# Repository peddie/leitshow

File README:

0) Purpose

This project is a music-synced lightshow.  It attempts to map an audio
stream onto a series of intensity commands for channels, presumably
then connected to lights, in a way that makes the light/music
combination entertaining.

1) Build process

Type `make'.  

You will need FFTW3 and PulseAudio development files installed; on
civilized systems these are available as `libfftw3-dev' and
`libpulse-dev'.  The makefile wants gcc-4.5; if you don't have it, you
can change that to just `gcc' and remove `-flto' from the definition
of `OPTFLAGS'.  

1.1) Portability

Nope.  

2) Usage

Type `./leitshow'.  

You will most likely want the PulseAudio utility called `pavucontrol',
which lets you choose what audio stream to send to the lightshow
program.  When I don't explicitly assign a channel with pavucontrol,
pulseaudio seems to give the lightshow the microphone audio stream by
default.

3) Customization

The lightshow will attempt to send commands via /dev/ttyUSB0.  You can
change this, along with the number of channels and a few other things,
in the #defines section at the beginning of `test.c'.

4) Hardware

The hardware matters little, as long as you have a device that can
listen for the code word and then read channel intensities and turn
them into fet duty cycles.

4.1) Example setup (at the Oasis):

Henry set up a bunch of cheap LED rolls from china to be driven by a
dsPIC motor controller board.  We elected to use 3 channels (R, G, B),
so the PIC simply receives the code word followed by 3 8-bit values
that indicate the desired intensity for each channel.  The motor
controller board already has 3 channels for driving brushless motors,
so we just directly translate the intensity commands to duty cycles.
We connect the LED rolls to a 12V power supply through the motor
control phases, and we're done.  

5) Bugs

PulseAudio seems to like to send the program the microphone stream
rather than the music stream.  Not sure if this can be worked around
or if I need to switch to using JACK.  

The lightshow doesn't work that well as a music-synced lightshow; it's
not that enjoyable to watch.  More algorithm development is needed.

6) Thanks

This lightshow is a crappy approximation of the one at tEp at MIT.
Almost every aspect of it was inspired by the tEp one, and if I hadn't
worked on a few of the incarnations of the tEp lightshow, this would
have taken a lot longer.  That lightshow was written, at various
times, by Frostbyte, Penguin, sMark, Elmo and Knosepiq.

Henry Hallam, as is his custom, got all the hardware working in a
remarkably short period of time.

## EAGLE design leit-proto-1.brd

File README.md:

leitshow
========

Light show PCBs (and code?)

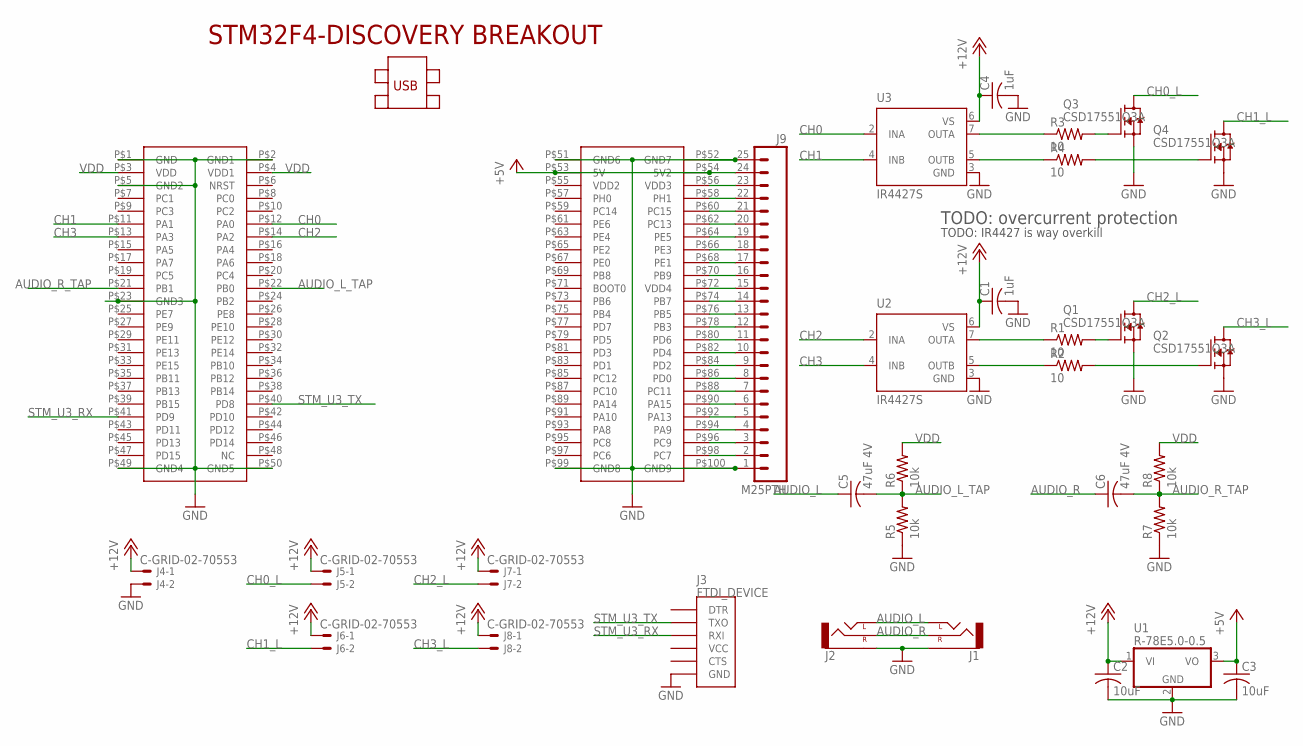
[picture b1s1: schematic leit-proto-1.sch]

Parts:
C1, C4: 1uF; C0603
C2, C3: 10uF; C0805
C5, C6: 47uF 4V; C0805
J1, J2: AUDIO-JACKPTH; AUDIO-JACK
J3: FTDI_DEVICE; FTDI_DEVICE_SIDE
J4, J5, J6, J7, J8: C-GRID-02-70553; 70553-02
J9: M25PTH; 1X25
MOD1: STM32F4-DISCOVERY
Q1, Q2, Q3, Q4: CSD17551Q3A; SON3.3
R1, R2, R3, R4: 10; R0603
R5, R6, R7, R8: 10k; R0603
U1: R-78E5.0-0.5; TO220V
U2, U3: IR4427S; SO08

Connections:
+5V: C3.1, J9.24, MOD1.P$53 (5V), MOD1.P$54 (5V2), U1.3 (VO)
+12V: C1.1, C2.1, C4.1, J4.1, J5.1, J6.1, J7.1, J8.1, U1.1 (VI), U2.6 (VS), U3.6 (VS)
AUDIO_L: C5.1, J1.TIP (LEFT), J2.TIP (LEFT)
AUDIO_L_TAP: C5.2, MOD1.P$22 (PB0), R5.2, R6.1
AUDIO_R: C6.1, J1.RING (RIGHT), J2.RING (RIGHT)
AUDIO_R_TAP: C6.2, MOD1.P$21 (PB1), R7.2, R8.1
CH0: MOD1.P$12 (PA0), U3.2 (INA)
CH0_L: J5.2, Q3.5 (D), Q3.6 (D), Q3.7 (D), Q3.8 (D)
CH1: MOD1.P$11 (PA1), U3.4 (INB)
CH1_L: J6.2, Q4.5 (D), Q4.6 (D), Q4.7 (D), Q4.8 (D)
CH2: MOD1.P$14 (PA2), U2.2 (INA)
CH2_L: J7.2, Q1.5 (D), Q1.6 (D), Q1.7 (D), Q1.8 (D)
CH3: MOD1.P$13 (PA3), U2.4 (INB)
CH3_L: J8.2, Q2.5 (D), Q2.6 (D), Q2.7 (D), Q2.8 (D)
GND: C1.2, C2.2, C3.2, C4.2, J1.SLEEVE, J2.SLEEVE, J3.P$6 (GND), J4.2, J9.1, J9.25, MOD1.P$1 (GND), MOD1.P$2 (GND1), MOD1.P$5 (GND2), MOD1.P$23 (GND3), MOD1.P$49 (GND4), MOD1.P$50 (GND5), MOD1.P$51 (GND6), MOD1.P$52 (GND7), MOD1.P$99 (GND8), MOD1.P$100 (GND9), Q1.1 (S), Q1.2 (S), Q1.3 (S), Q2.1 (S), Q2.2 (S), Q2.3 (S), Q3.1 (S), Q3.2 (S), Q3.3 (S), Q4.1 (S), Q4.2 (S), Q4.3 (S), R5.1, R7.1, U1.2 (GND), U2.3 (GND), U3.3 (GND)
unnamed: R1.1, U2.7 (OUTA)
unnamed: Q1.4 (G), R1.2
unnamed: Q2.4 (G), R2.2
unnamed: R2.1, U2.5 (OUTB)
unnamed: R3.1, U3.7 (OUTA)
unnamed: Q3.4 (G), R3.2
unnamed: Q4.4 (G), R4.2
unnamed: R4.1, U3.5 (OUTB)
unnamed: J9.2, MOD1.P$98 (PC7)
unnamed: J9.3, MOD1.P$96 (PC9)
unnamed: J9.4, MOD1.P$94 (PA9)
unnamed: J9.5, MOD1.P$92 (PA13)
unnamed: J9.6, MOD1.P$90 (PA15)
unnamed: J9.7, MOD1.P$88 (PC11)
unnamed: J9.8, MOD1.P$86 (PD0)
unnamed: J9.9, MOD1.P$84 (PD2)
unnamed: J9.10, MOD1.P$82 (PD4)
unnamed: J9.11, MOD1.P$80 (PD6)
unnamed: J9.12, MOD1.P$78 (PB3)
unnamed: J9.13, MOD1.P$76 (PB5)
unnamed: J9.14, MOD1.P$74 (PB7)
unnamed: J9.15, MOD1.P$72 (VDD4)
unnamed: J9.16, MOD1.P$70 (PB9)
unnamed: J9.17, MOD1.P$68 (PE1)
unnamed: J9.18, MOD1.P$66 (PE3)
unnamed: J9.19, MOD1.P$64 (PE5)
unnamed: J9.20, MOD1.P$62 (PC13)
unnamed: J9.21, MOD1.P$60 (PC15)
unnamed: J9.22, MOD1.P$58 (PH1)
unnamed: J9.23, MOD1.P$56 (VDD3)
STM_U3_RX: J3.P$3 (RXI), MOD1.P$41 (PD9)
STM_U3_TX: J3.P$2 (TXO), MOD1.P$40 (PD8)
VDD: MOD1.P$3 (VDD), MOD1.P$4 (VDD1), R6.2, R8.2

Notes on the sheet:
TODO: overcurrent protection
TODO: IR4427 is way overkill

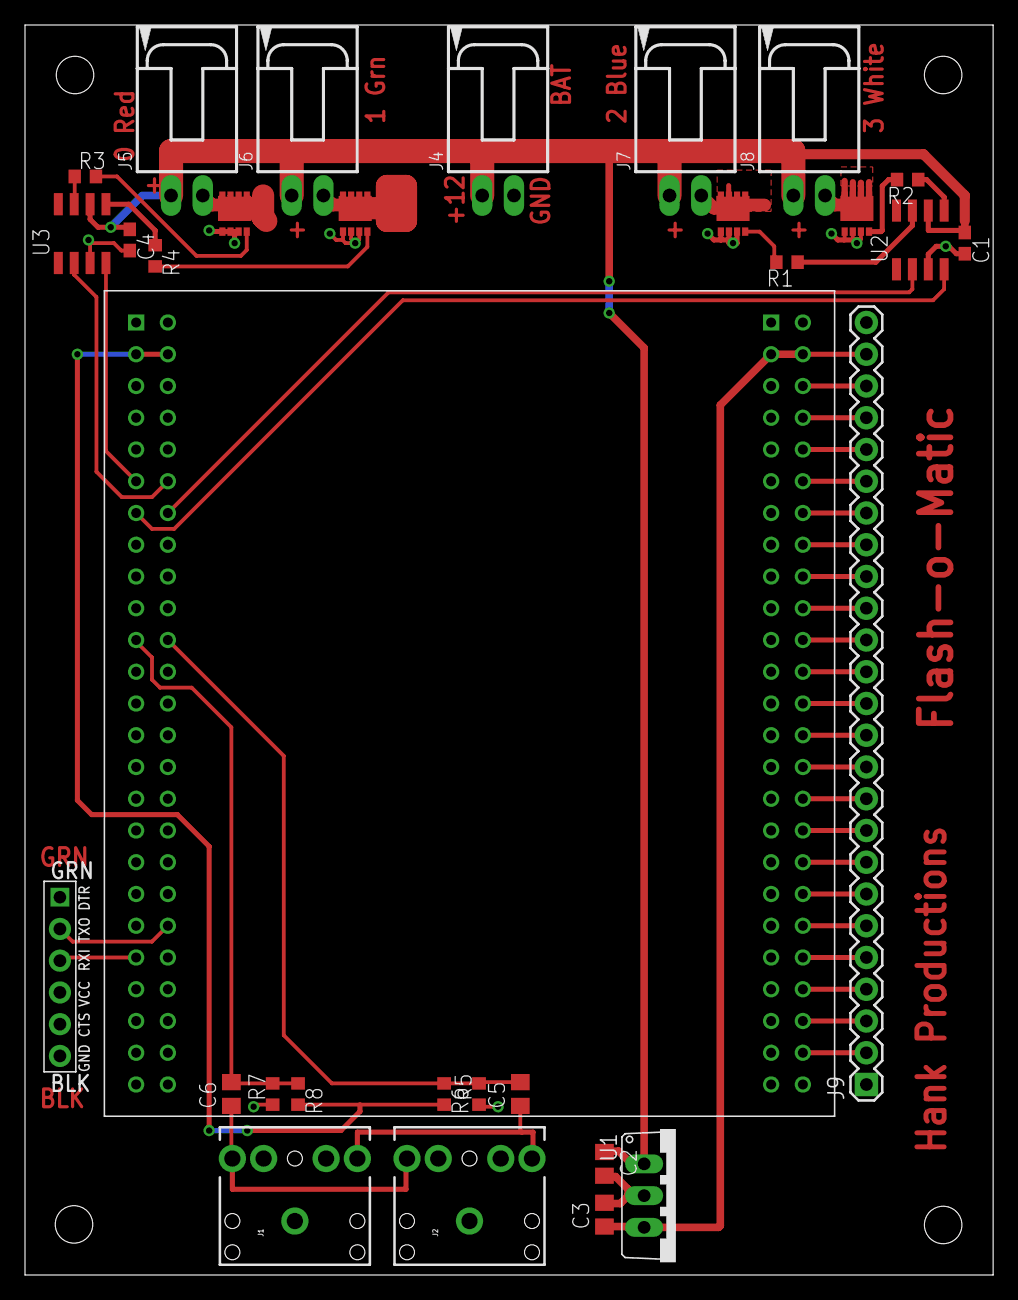
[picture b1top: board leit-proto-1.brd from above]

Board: 2 copper layers, 77.5 x 100.0 mm, 31 parts (0 on the bottom side), 48 nets.

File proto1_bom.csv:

Part,Value,Device,Package,Description,DK order code,DK qty,DK ref
C1,1uF,C-USC0603,C0603,"CAPACITOR, American symbol",311-1372-1-ND,10,Leitshow C1 C4
C2,10uF,C-USC0805,C0805,"CAPACITOR, American symbol",1276-2893-1-ND,10,Leitshow C2 C3
C3,10uF,C-USC0805,C0805,"CAPACITOR, American symbol",-,,
C4,1uF,C-USC0603,C0603,"CAPACITOR, American symbol",-,,
C5,47uF 4V,C-USC0805,C0805,"CAPACITOR, American symbol",445-5987-1-ND,10,Leitshow C5 C6
C6,47uF 4V,C-USC0805,C0805,"CAPACITOR, American symbol",-,,
J1,,AUDIO-JACKPTH,AUDIO-JACK,3.5mm Audio Jack,CP1-3523NG-ND,10,LEITSHOW J1 J2
J2,,AUDIO-JACKPTH,AUDIO-JACK,3.5mm Audio Jack,-,,
J3,FTDI_DEVICE,FTDI_DEVICE,FTDI_DEVICE_SIDE,Connector which mates to FTDI basic or FTDI cable.,-,,
J4,C-GRID-02-70553,C-GRID-02-70553,70553-02,CONNECTOR,WM4900-ND,15,LEITSHOW J4-J8
J5,C-GRID-02-70553,C-GRID-02-70553,70553-02,CONNECTOR,-,,
J6,C-GRID-02-70553,C-GRID-02-70553,70553-02,CONNECTOR,-,,
J7,C-GRID-02-70553,C-GRID-02-70553,70553-02,CONNECTOR,-,,
J8,C-GRID-02-70553,C-GRID-02-70553,70553-02,CONNECTOR,-,,
J9,M25PTH,M25PTH,1X25,"1x25 .1"" header",-,,
MOD1,STM32F4-DISCOVERY,STM32F4-DISCOVERY,STM32F4-DISCOVERY,,497-11455-ND,2,Leitshow MOD1
Q1,CSD17551Q3A,CSD17551Q3A,SON3.3,"CSD17551Q3A 30V, N-Channel NexFET Power MOSFET",296-35025-1-ND,10,Leitshow Q1-Q4
Q2,CSD17551Q3A,CSD17551Q3A,SON3.3,"CSD17551Q3A 30V, N-Channel NexFET Power MOSFET",-,,
Q3,CSD17551Q3A,CSD17551Q3A,SON3.3,"CSD17551Q3A 30V, N-Channel NexFET Power MOSFET",-,,
Q4,CSD17551Q3A,CSD17551Q3A,SON3.3,"CSD17551Q3A 30V, N-Channel NexFET Power MOSFET",-,,
R1,10,R-US_R0603,R0603,"RESISTOR, American symbol",1276-5014-1-ND,25,Leitshow R1-R4
R2,10,R-US_R0603,R0603,"RESISTOR, American symbol",-,,
R3,10,R-US_R0603,R0603,"RESISTOR, American symbol",-,,
R4,10,R-US_R0603,R0603,"RESISTOR, American symbol",-,,
R5,10k,R-US_R0603,R0603,"RESISTOR, American symbol",311-10KGRCT-ND,,Leitshow R5-R8
R6,10k,R-US_R0603,R0603,"RESISTOR, American symbol",-,,
R7,10k,R-US_R0603,R0603,"RESISTOR, American symbol",-,,
R8,10k,R-US_R0603,R0603,"RESISTOR, American symbol",-,,
U1,R-78E5.0-0.5,7805TV,TO220V,Positive VOLTAGE REGULATOR,945-1648-5-ND,5,LEITSHOW U1
U2,IR4427S,IR4427S,SO08,DUAL LOW SIDE DRIVER,IR4427SPBF-ND,10,Leitshow U2 U3
U3,IR4427S,IR4427S,SO08,DUAL LOW SIDE DRIVER,-,,
Socket for discovery board,,,,,S9201-ND,6,LEITSHOW MOD1 SOCKET
Connector housings,,,,,WM2900-ND,25,Leitshow
Connector crimp pins,,,,,WM2510CT-ND,50,Leitshow

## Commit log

2011-03-13 initial commit, after the Oasis housewarming party
2011-03-13 fix typo in makefile
2011-03-13 add handy ignore file
2011-03-14 Cleanup and documentation
2011-03-14 A ton of changes; reorganization into processing phases.
2011-03-14 A bunch more work, and a bit of tuning against a variety of music.
2011-04-02 Reorganize project into multiple files
2012-06-18 A few touch-ups and some tuning.
2012-06-18 new readme file
2012-06-18 Enable debug symbols (oops!)
2012-06-18 Rename test.c to leitshow.c
2012-06-18 Refactor the main program big time; introduce bin boundaries and separate out statistics calculation.
2012-06-18 huge update -- work in progress. I think the Fourier basis is not a good basis to try to decorrelate the channels in if you're listening to music.
2012-06-18 fix a minor bug and add lots of debug output
2012-06-18 readme fixes
2012-06-26 Important definitions
2012-06-26 Makefile tidying -- add config.h and arraymath.h as dependencies
2012-06-26 Add adaptive thresholding for channels
2012-06-26 Separate out low-pass filtering from calculation of statistics
2012-06-26 Add adaptive gains per channel to keep all channels active
2012-06-26 Tuning
2012-06-26 Add differentiation and decorrelation
2012-06-26 documentation updates
2012-09-29 Set the latency on the pulseaudio stream to be much faster than the default of 2 seconds for smooth playback.
2012-09-29 Remove sse4.1 flag from makefile; was breaking other people's builds
2012-10-14 Add a check so that if the show encounters silence for a while, it won't keep adapting.
2013-06-10 Readjust bin boundaries to be a bit more harmonic; simplify and tune things a bit.
2013-06-10 Update printouts
2013-06-10 Makefile improvements.
2013-06-10 linter fixes
2013-06-10 Remove useless OUTPUT_PRESCALE
2013-06-10 Re-enable variable buffer sizes
2013-08-19 schematic complete for first prototype
2013-08-19 PCB layout complete for barebones proto
2013-08-19 Add BOM for prototype
2013-08-24 better solder paste for transistor?
2013-08-24 software
2013-08-24 blinkenlichten
2013-08-25 leitshow prototypes
2013-08-25 Add filterbank code for Cortex-M4 using CMSIS (kind of crappy)
2013-08-25 Remove CMSIS dependency with built-in biquad code
2013-08-25 Trivial analysis code to get started.
2013-08-25 revert makefile dir
2013-08-25 filter init
2013-08-25 nans
2013-08-25 Working quite nicely
2013-08-25 Always print out sample time to avoid confusion
2013-08-25 A quick test program for the filter bank.
2013-08-25 Make it so you can check CPU load from GDB
2013-08-25 Contrary to the comment in the code, adding diff_bins() from the PC leitshow makes things chill.
2013-08-25 This doesn't need to be so fast.
2013-08-25 A few more tune-ups.
2013-08-25 a touch of dubstep tuning
2017-01-28 Upgrade Makefile to the new system.
2017-01-28 Filter bank debug output changes
2017-01-28 Part 2 of filter bank debug changes
2017-01-28 Assorted cleanups
2017-01-28 Decouple the number of FFT bins from the number of output channels
2017-01-28 Integrate PCA analysis routine (not pretty yet)
2017-01-29 KICK ASS ON HW
2017-01-31 Actually add PCA files

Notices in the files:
parts and their libraries:
SparkFun-Connectors: Licensing: CC v3.0 Share-Alike You are welcome to use this library for commercial purposes.
